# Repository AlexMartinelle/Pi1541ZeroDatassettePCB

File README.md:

# Pi1541ZeroDatassettePCB
PCB design for a Pi11541 hat for the Raspberry Pi Zero with additional datassette IO support.

I wanted a Pi1541 hat for the Raspberry Pi Zero that had proper serial ports
and the pins to support my datassette support for the Pi1541.
Datasette code available at: https://github.com/AlexMartinelle/Pi1541DatassetteSupport

This PCB is designed to be used with the Pi1541 Option B settings but with one extra tweak,
the i2cBusMaster setting should be zero since it uses pin 27 for SDA, and pin 28 for SCL.

The gerbers are also available from PCBWay at https://www.pcbway.com/project/shareproject/Pi1541_option_B_hat_for_Raspberry_Pi_Zero_with_datassette_IO_support_94f0028b.html

The design is loosely based on the https://github.com/hackup/Pi1541io PCB and the components used on that PCB.

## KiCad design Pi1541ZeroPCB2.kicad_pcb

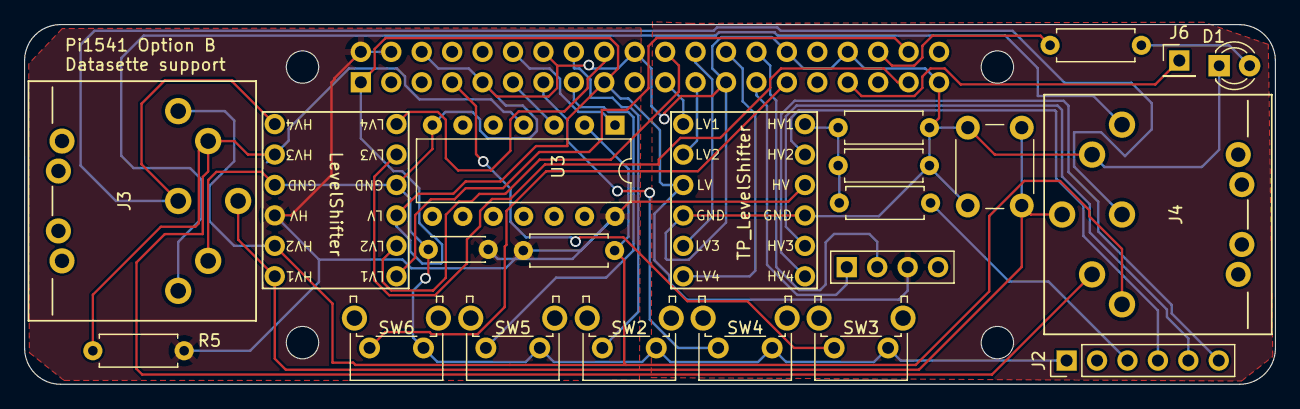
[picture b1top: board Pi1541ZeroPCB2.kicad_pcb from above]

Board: 2 copper layers, 104.4 x 30.0 mm, 27 parts (1 on the bottom side), 33 nets.

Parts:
C1: 100n; C_Disc_D4.3mm_W1.9mm_P5.00mm
D1: ACT; LED_D3.0mm
J1: GPIO; PinSocket_2x20_P2.54mm_Vertical
J2: TP_PORT_C64; PinHeader_1x06_P2.54mm_Vertical
J3: IEC1; DIN-6-Variable
J4: IEC2; DIN-6-Variable
J5: I2C; Socket_Strip_Straight_1x04_Pitch2.54mm
J6: ExtSpkr; PinHeader_1x01_P2.54mm_Vertical
MH1, MH2, MH3, MH4: MountingHole_2.7mm_M2.5
R1: 1K; R_Axial_DIN0207_L6.3mm_D2.5mm_P7.62mm_Horizontal
R2: 4.7K; R_Axial_DIN0207_L6.3mm_D2.5mm_P7.62mm_Horizontal
R3, R6: 220; R_Axial_DIN0207_L6.3mm_D2.5mm_P7.62mm_Horizontal
R4, R5: 1k; R_Axial_DIN0207_L6.3mm_D2.5mm_P7.62mm_Horizontal
SW1: Reset; SW_PUSH_6mm
SW2: Next_Btn; SW_Tactile_SPST_Angled_PTS645Vx83-2LFS
SW3: Exit_Btn; SW_Tactile_SPST_Angled_PTS645Vx83-2LFS
SW4: Select_Btn; SW_Tactile_SPST_Angled_PTS645Vx83-2LFS
SW5: Prev_Btn; SW_Tactile_SPST_Angled_PTS645Vx83-2LFS
SW6: Insert_Btn; SW_Tactile_SPST_Angled_PTS645Vx83-2LFS
U1: TP_LevelShifter; LevelShifterModule4CH
U2: LevelShifter; LevelShifterModule4CH
U3: 7406; DIP-14_W7.62mm

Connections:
+3V3: J1.1, J1.17, J5.3, U1.3 (LV), U2.3 (LV)
+5V: C1.1, J1.2, J1.4, R4.1, R5.1, U1.10 (HV), U2.10 (HV), U3.14 (Vcc)
/GPIO4/GPCLK0: J1.7, SW3.2
/GPIO5: J1.29, SW6.2
/GPIO13/PWM1: J1.33, J6.1
/GPIO16: J1.36, R6.1
/GPIO22: J1.15, SW5.2
/GPIO23: J1.16, SW2.2
/GPIO27: J1.13, SW4.2
ATN: J3.3, J4.3, U2.7 (HV4)
ATN_IN: J1.18, U2.6 (LV4)
CLK: J3.4, J4.4, R5.2, U2.8 (HV3), U3.4
CLK_BD: J1.11, U3.3
CLK_IN: J1.37, U2.5 (LV3)
DATA: J3.5, J4.5, R4.2, U2.11 (HV2), U3.2
DATA_BD: J1.12, U3.1
DATA_IN: J1.22, U2.2 (LV2)
GND: C1.2, D1.1 (K), J1.6, J1.9, J1.14, J1.20, J1.25, J1.30, J1.34, J1.39, J2.1, J3.2, J4.2, J5.4, R1.2, R2.2, SW1.2, SW2.1, SW3.1, SW4.1, SW5.1, SW6.1, U1.4 (GND), U1.9 (GND), U2.4 (GND), U2.9 (GND), U3.7 (Gnd)
I2C0_SCL: J1.28, J5.2
I2C0_SDA: J1.27, J5.1
unnamed: D1.2 (A), R6.2
unnamed: J2.3, R3.1
RESET: J3.6, J4.6, SW1.1, U2.12 (HV1)
RESET_IN: J1.38, U2.1 (LV1)
SRQ: J3.1, J4.1
TP_MOTOR_3V: J1.21, U1.1 (LV1)
TP_MOTOR_6V: R1.1, R2.1, R3.2, U1.12 (HV1)
TP_READ_3V: J1.23, U1.2 (LV2)
TP_READ_5V: J2.4, U1.11 (HV2)
TP_SENSE_3V: J1.26, U1.6 (LV4)
TP_SENSE_5V: J2.6, U1.7 (HV4)
TP_WRITE_3V: J1.24, U1.5 (LV3)
TP_WRITE_5V: J2.5, U1.8 (HV3)

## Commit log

2023-10-11 Initial check-in
